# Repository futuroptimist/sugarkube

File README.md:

# 🍧 sugarkube

[![hardware boot][hardware-boot-badge]][pi-smoke-test-doc]

An accessible [k3s](https://k3s.io/) platform for Raspberry Pis and SBCs,
integrated with an off-grid solar setup.
The repository also covers the solar cube art installation, which powers aquarium air pumps and
small computers. It doubles as a living trellis—climbing plants weave through the aluminium
extrusions, while shade-loving herbs thrive beneath the panels. Hanging baskets can clip onto the
frame so the installation is surrounded by greenery.

### What's in a name?

"Sugarkube" refers to both the aluminium cube covered in solar panels **and**
the helper scripts that provide "syntactic sugar" for Kubernetes. Throughout
the docs you will see the term used in both contexts. The physical cube is
designed to be saturated with greenery: ground-level pots and grow bags tuck
between the uprights while hanging planters fill the airspace. Hardy
fruiting plants such as strawberries thrive in this arrangement and literally
embed glucose, fructose, and sucrose—the sugars that inspired the name—into the
structure's living canopy.

## Quick start: 3-node HA k3s cluster

New to sugarkube? Start with the 3-node HA happy path and follow it end-to-end:

- **[Happy path: 3-server HA cluster in two runs](docs/raspi_cluster_setup.md#happy-path-3-server-ha-cluster-in-two-runs)**
  — download the latest Pi image, flash, clone to SSD, bring up dev/staging/prod, and verify the
  cluster.
- **[Raspberry Pi cluster series](docs/index.md#raspberry-pi-cluster-series)** — Part 1/Part 2
  quick-starts plus manual walkthroughs when you want the raw commands.

## Application runbooks

- **[Generic app deployment contract](docs/app_deployment_contract.md)** — shared artifact,
  tag, chart, app-config, and `just app-*` command contract for all Sugarkube apps.
- **[Observability design](docs/observability-design.md)** — canonical Prometheus/Grafana
  design, ownership contract, privacy rules, dashboards, alerts, and release gates for Sugarkube,
  DSPACE, token.place, and danielsmith.io.
- **[Production power and network reliability](docs/production-power-network-reliability.md)**
  — draft cellular and battery design, measurement plan, and human validation gates.
- **[Node interface selection design](docs/node-interface-selection-design.md)**
  — K341 Ethernet/WiFi proposal, identity and quorum constraints, and qualification gates.
- **[Future-app onboarding guide](docs/app_onboarding.md)** — checklist and decision tree for
  adding apps such as wove and later services.
- **Current app runbooks** use the same GHCR-first staging, verification,
  promotion, rollback, and troubleshooting flow:
  - [DSPACE runbook](docs/apps/dspace.md) for `ghcr.io/democratizedspace/dspace`:
    [image workflow](https://github.com/democratizedspace/dspace/actions/workflows/ci-image.yml),
    [image package](https://github.com/democratizedspace/dspace/pkgs/container/dspace),
    [chart workflow](https://github.com/democratizedspace/dspace/actions/workflows/ci-helm.yml),
    [chart package listing](https://github.com/orgs/democratizedspace/packages?repo_name=dspace&q=charts%2Fdspace) (chart package page pending).
  - [token.place runbook](docs/apps/tokenplace.md) for `ghcr.io/futuroptimist/tokenplace-relay`:
    [image workflow](https://github.com/futuroptimist/token.place/actions/workflows/ci-image.yml),
    [image package](https://github.com/futuroptimist/token.place/pkgs/container/tokenplace-relay),
    [chart workflow](https://github.com/futuroptimist/token.place/actions/workflows/ci-helm.yml),
    [chart package](https://github.com/futuroptimist/token.place/pkgs/container/charts%2Ftokenplace).
  - [danielsmith.io runbook](docs/apps/danielsmith.md) for `ghcr.io/futuroptimist/danielsmith.io`:
    [image workflow](https://github.com/futuroptimist/danielsmith.io/actions/workflows/ci-image.yml),
    [image package](https://github.com/futuroptimist/danielsmith.io/pkgs/container/danielsmith.io),
    [chart workflow](https://github.com/futuroptimist/danielsmith.io/actions/workflows/ci-helm.yml),
    [chart package](https://github.com/futuroptimist/danielsmith.io/pkgs/container/charts%2Fdanielsmith).
  - [GitShelves runbook](docs/apps/gitshelves.md) for `ghcr.io/futuroptimist/gitshelves`:
    [image workflow](https://github.com/futuroptimist/gitshelves/actions/workflows/ci-image.yml),
    [image package](https://github.com/futuroptimist/gitshelves/pkgs/container/gitshelves),
    [chart workflow](https://github.com/futuroptimist/gitshelves/actions/workflows/ci-helm.yml),
    [chart package](https://github.com/futuroptimist/gitshelves/pkgs/container/charts%2Fgitshelves).
  - [jobbot3000 runbook](docs/apps/jobbot3000.md) for `ghcr.io/futuroptimist/jobbot3000`:
    [image workflow](https://github.com/futuroptimist/jobbot3000/actions/workflows/ci-image.yml),
    [image package](https://github.com/futuroptimist/jobbot3000/pkgs/container/jobbot3000),
    [chart workflow](https://github.com/futuroptimist/jobbot3000/actions/workflows/ci-helm.yml),
    [chart package](https://github.com/futuroptimist/jobbot3000/pkgs/container/charts%2Fjobbot3000).
- **Environment shortcuts:** token.place
  [dev](docs/k3s-tokenplace-dev.md), [staging](docs/k3s-tokenplace-staging.md), and
  [production](docs/k3s-tokenplace-prod.md); danielsmith.io
  [staging](docs/k3s-danielsmith-staging.md) and
  [production](docs/k3s-danielsmith-prod.md).

## Repository layout

- `cad/` — OpenSCAD models of structural parts. See
  [docs/pi_cluster_carrier.md](docs/pi_cluster_carrier.md) for the Pi carrier plate,
  [cad/solar_cube/panel_bracket.scad](cad/solar_cube/panel_bracket.scad) for the solar
  panel bracket with an `edge_radius` parameter (default 4 mm) to round its outer edges,
  and [cad/solar_cube/frame.scad](cad/solar_cube/frame.scad) for a parametric 2020 cube frame.
- `elex/` — KiCad and Fritzing electronics schematics including the `power_ring`
  board (see [elex/power_ring/specs.md](elex/power_ring/specs.md) and
  [docs/electronics_schematics.md](docs/electronics_schematics.md))
- `hardware/` — accessories like the Mac mini keyboard station cap (see
  [docs/mac_mini_station.md](docs/mac_mini_station.md))
- `docs/` — build instructions, safety notes, and learning resources
- [docs/start-here.md](docs/start-here.md) — quick orientation with 15-minute,
  day-one, and advanced reference tracks
- [docs/solar_basics.md](docs/solar_basics.md) — introduction to how solar panels generate
  power
- [docs/electronics_basics.md](docs/electronics_basics.md) — essential circuits and tools
- [docs/power_system_design.md](docs/power_system_design.md) — sizing batteries and
  charge controllers
- [docs/insert_basics.md](docs/insert_basics.md) — guide for heat-set inserts and printed threads
- [docs/network_setup.md](docs/network_setup.md) — connect the Pi cluster to your network
- [docs/lcd_mount.md](docs/lcd_mount.md) — optional 1602 LCD standoff locations
- [docs/pi_headless_provisioning.md](docs/pi_headless_provisioning.md) — headless boot playbook for
  `secrets.env` usage
- [docs/pi_carrier_launch_playbook.md](docs/pi_carrier_launch_playbook.md) — end-to-end launch
  playbook with a 10-minute fast path, persona walkthroughs, and deep reference maps
- [docs/pi_image_quickstart.md](docs/pi_image_quickstart.md) — build, flash, and boot the image
- [docs/pi_image_contributor_guide.md](docs/pi_image_contributor_guide.md) — map automation helpers
  to the docs that describe them
- [docs/pi_carrier_field_guide.md](docs/pi_carrier_field_guide.md) — printable checklist with a PDF
  companion (`docs/pi_carrier_field_guide.pdf`) for the workbench
- [user-data example](docs/templates/cloud-init/user-data.example) — SSH key and WiFi template
- `scripts/` — helper scripts for rendering and exports. See
  [docs/contributor_script_map.md](docs/contributor_script_map.md) for a
  contributor-facing map that ties each helper to the guide that explains it.
  - `download_pi_image.sh` — fetch the latest Pi image via the GitHub CLI; supports `--dry-run`
    metadata checks and reconciles `--dir`/`--output` directories with POSIX `test -ef`
    instead of `realpath` so macOS-friendly symlinks work without extra tooling.
    Invoke it from the unified CLI with
    `python -m sugarkube_toolkit pi download [--dry-run] [helper args...]` when you prefer
    a consistent entry point across automation helpers. The unified CLI always runs helpers
    from the repository root so relative paths to `scripts/` and docs work even when you
    launch it from nested directories. `tests/test_cli_docs_repo_root.py` guards the docs
    call-out by invoking `monkeypatch.chdir` to enter a temporary folder before
    running both `docs verify` and `docs simplify`. If you prefer, you can also run
    `python -m` commands from the repository root so the package can be imported cleanly;
    from a nested directory, `./scripts/sugarkube ...` (or adding `scripts/` to your `PATH`)
    bootstraps `PYTHONPATH` before forwarding to the CLI. Either way, the CLI executes
    helpers from the repository root so relative paths to scripts and docs remain stable.
  - `install_sugarkube_image.sh` — install the GitHub CLI when missing, download the
    latest release, verify checksums, expand the `.img.xz`, and emit a new
    `.img.sha256`; safe to run via `curl | bash`. Pass `--dry-run` to print the
    download/expansion plan without touching disk. Invoke it from the unified CLI with
    `python -m sugarkube_toolkit pi install [--dry-run] [helper args...]` when you want
    the same behavior without leaving the `sugarkube` entry point.
  - `collect_pi_image.sh` — normalize pi-gen output into a single `.img.xz`,
    clean up temporary work directories, use POSIX `test -ef` to compare paths
    without `realpath`, and fall back to `unzip` when `bsdtar` is unavailable
  - `build_pi_image.sh` — build a Raspberry Pi OS image with cloud-init and
    k3s preinstalled; embeds `pi_node_verifier.sh`, clones `token.place` and
    `democratizedspace/dspace` by default, and now ships node exporter,
    cAdvisor, Grafana Agent, and Netdata containers for observability. Customize
    branches with `TOKEN_PLACE_BRANCH` (default `main`) and `DSPACE_BRANCH`
    (default `v3`). Set `CLONE_SUGARKUBE=true` to include this repo and pass
    space-separated Git URLs via `EXTRA_REPOS` to clone additional projects;
    needs a valid `user-data.yaml` and ~10 GB free disk space. Set `DEBUG=1` to
    trace script execution.
  - `flash_pi_media.sh` — stream `.img` or `.img.xz` directly to removable
    media with SHA-256 verification and automatic eject. A PowerShell wrapper
    (`flash_pi_media.ps1`) shells out to the same Python core on Windows.
  - `pi_node_verifier.sh` — check k3s prerequisites; use `--json` for machine output,
    `--full` to print text plus the JSON summary in one run, or `--help` for usage
  - `pi_smoke_test.py` — SSH wrapper that runs the verifier remotely, supports reboot checks,
    and emits JSON summaries for CI harnesses
  - `collect_support_bundle.py` — gather Kubernetes, systemd, and Docker diagnostics into timestamped
    archives. Invoke it from the unified CLI with
    `python -m sugarkube_toolkit pi support-bundle [--dry-run] [args...]` when you want the same
    workflow without leaving the `sugarkube` entry point. The CLI `--dry-run` flag prints the
    helper invocation without executing it so you can confirm the host and arguments before running
    the collection (guarded by
    `tests/test_sugarkube_toolkit_cli.py::test_pi_support_bundle_invokes_helper`).
  - `sugarkube_doctor.sh` — chain download dry-runs, flash validation, and linting checks. Invoke it
    from the unified CLI with `python -m sugarkube_toolkit doctor [--dry-run] [-- args...]` to avoid
    memorizing the standalone helper.
  - `render_field_guide_pdf.py` — build the Markdown field guide into a single-page PDF without
    extra pip dependencies so releases can refresh the printable checklist automatically
  - `scan-secrets.py` — scan diffs for high-risk patterns using `ripsecrets` when
    available and also run a regex check to catch common tokens
- `outages/` — structured outage records (see
  [docs/outage_catalog.md](docs/outage_catalog.md))
- `tests/` — quick checks for helper scripts and documentation

## Pi image releases

Use the `pi-image` workflow when you need a fresh on-demand workflow artifact
for reimaging Raspberry Pi nodes; open **Actions → pi-image → Run workflow** (or let the
cluster bootstrap helper dispatch it) and download the `sugarkube-img` artifact.
Use `pi-image-release` only when a maintainer intentionally needs to publish the
latest signed GitHub Release. That manual release-publisher workflow builds the
image, optionally boots it in QEMU, signs release assets with cosign when
publishing is enabled, and attaches `sugarkube.img.xz`, its checksum, a
provenance manifest, and the full `pi-gen` build log to the release. Release
notes summarize stage timings and link directly to the manifest so you can
verify the build inputs and commit hashes before flashing. Run
`./scripts/install_sugarkube_image.sh` (or fetch the same helper
 via `curl -fsSL https://raw.githubusercontent.com/futuroptimist/sugarkube/main/scripts/install_sugarkube_image.sh | bash`) to
 download, verify, and expand the latest release. When you prefer a task runner,
use either `sudo make flash-pi FLASH_DEVICE=/dev/sdX` or `sudo FLASH_DEVICE=/dev/sdX just flash-pi` to
chain download → verification → flashing with the streaming helper. Prefer go-task? Run
`sudo task pi:flash FLASH_DEVICE=/dev/sdX` to reach the same helper via the Taskfile. Need to forward
additional helper flags? Append `PI_FLASH_ARGS="-- --force"` (or similar) alongside `FLASH_DEVICE`
so both the device and extra arguments are preserved. The recipe variables read `FLASH_DEVICE`
(and optional `DOWNLOAD_ARGS`) from the environment, so prefix the variable as shown. Regression coverage:
`tests/test_taskfile.py::test_taskfile_pi_flash_forwards_flash_device` keeps the go-task wrapper aligned with
these instructions. Both the Makefile, justfile, and Taskfile expose
`download-pi-image`, `install-pi-image`,
`doctor`, and `codespaces-bootstrap`
shortcuts so GitHub
Codespaces users can install prerequisites and flash media without additional shell glue—pick the runner
you prefer (`make codespaces-bootstrap`, `just codespaces-bootstrap`, or `task codespaces-bootstrap`). Go-task
users can also call the hyphenated aliases directly (`task download-pi-image`, `task install-pi-image`),
which forward `DOWNLOAD_ARGS` the same way as the Make and just wrappers. Regression coverage:
`tests/test_codespaces_bootstrap.py` keeps the package lists aligned across each wrapper, and
`tests/test_taskfile.py::test_taskfile_includes_make_style_aliases` ensures the Taskfile mirrors the
documented shortcuts.
`./scripts/sugarkube-latest` remains available when you only need the `.img.xz` artifact with
checksum verification.
Prefer a unified entry point? Run `python -m sugarkube_toolkit pi download --dry-run` from the
repository root to preview the release helper. Once running, the CLI forces the working directory to
the repository root before invoking helpers. Working from a nested directory? Call
`./scripts/sugarkube pi download --dry-run` (or add `scripts/` to your `PATH`) so the wrapper
bootstraps `PYTHONPATH` before forwarding to the CLI. When prerequisites such as the GitHub CLI,
`curl`, or `sha256sum` are missing, the dry-run prints reminders instead of aborting so you can
review the planned commands first. Need the combined installer that downloads and
expands the image? Run

```bash
python -m sugarkube_toolkit pi install --dry-run -- --dir ~/sugarkube/images --image ~/sugarkube/images/sugarkube.img
```

Drop `--dry-run` once you are ready; flags after the standalone `--` flow directly to
`scripts/install_sugarkube_image.sh`.

Reuse the streaming helper via:

```bash
python -m sugarkube_toolkit pi flash --dry-run -- --image ~/sugarkube/images/sugarkube.img --device /dev/sdX
```

Drop `--dry-run` when you're ready to write media.

Prefer a guided experience? Open [docs/flash-helper/](docs/flash-helper/) to paste a workflow run
URL and receive OS-specific download, verification, and flashing steps. The same logic is also
available via `python scripts/workflow_flash_instructions.py --help` for command-line use.

Run `pre-commit run --all-files` before committing.
This triggers `scripts/checks.sh`, which installs required tooling and runs
linters, tests, and documentation checks. If you send patches with `git send-email`,
copy [`hooks/sendemail-validate.sample`](hooks/sendemail-validate.sample) to
`.git/hooks/sendemail-validate` so the email workflow executes the same checks
after applying your series and scans each patch for secrets before sending.
The helper now bootstraps the [`just`](https://github.com/casey/just) binary automatically when it
is missing so the formatting and orchestration recipes never skip; run
`./scripts/install_just.sh` directly when you want to install the tool ahead of the
full check suite.
Running the checks as a non-root user now exports `ALLOW_NON_ROOT=1` and sets
`BATS_CWD`/`BATS_LIB_PATH` to the repository root so Bats fixtures resolve the
same way they do in CI. Overriding `ALLOW_NON_ROOT` with any value other than
`1` causes an immediate failure instead of a confusing permission error.
Regression coverage:
`tests/test_sendemail_validate_hook.py::test_sendemail_hook_runs_repo_checks`
and
`tests/test_sendemail_validate_hook.py::test_sendemail_hook_scans_patches_for_secrets`,
plus `tests/checks_script_test.py::test_exports_test_env_defaults` and
`tests/checks_script_test.py::test_rejects_conflicting_allow_non_root`.

### Integration tests

Set `AVAHI_AVAILABLE=1` to opt into the Avahi-backed mDNS roundtrip test. The
integration suite expects `avahi-publish`, `avahi-browse`, and `avahi-resolve`
to be installed. Run it directly with:

```bash
AVAHI_AVAILABLE=1 bats tests/integration/mdns_roundtrip.bats
```

When you run the broader pytest suite in minimal containers, set
`SUGARKUBE_ALLOW_TOOL_SHIMS=1` to let `tests.conftest.require_tools` create
temporary stand-ins for missing binaries (for example, `ip` and `ping`). Provide
`SUGARKUBE_TOOL_SHIM_DIR=/tmp/shims` to control where the executables are
written. Shims are happy-path stubs that always return exit code ``0`` and the
shim directory is prepended to ``PATH`` while enabled, so prefer using them in
isolated test environments (such as disposable containers or dedicated
virtualenvs) instead of your daily shell. Regression coverage:
`tests/test_require_tools.py::test_require_tools_falls_back_to_shims`.
When installers are unavailable, `require_tools` now reuses the same shim
fallback controlled by `SUGARKUBE_PREINSTALL_TOOL_SHIMS` (defaults to `"1"`) so
per-test checks avoid skipping in constrained environments. Regression coverage:
`tests/test_require_tools.py::test_require_tools_shims_after_install_failure_with_preinstall_enabled`.
When `apt-get` is unavailable, the session-level pre-install hook now shims the
core CLI dependencies ahead of time so integration tests see the expected tools
without waiting for per-test skip handling. Set
`SUGARKUBE_PREINSTALL_TOOL_SHIMS=0` to opt out when you need to exercise real
installations instead of stubs. Regression coverage:
`tests/test_require_tools.py::test_preinstall_test_cli_tools_shims_when_installs_blocked`
and `tests/test_require_tools.py::test_preinstall_test_cli_tools_shim_opt_out`.
Network namespace probes now request the `ip` and `unshare` utilities up front,
falling back to the same tooling installer before retrying with sudo so CI and
local runs converge. Regression coverage:
`tests/test_ensure_root_privileges.py::test_ensure_root_privileges_installs_netns_tools_first`.
Set `SUGARKUBE_NETNS_FALLBACK=xfail` when you want missing network namespace
privileges to be recorded as expected failures instead of skips so the suite
highlights the capability gap without hiding it. Regression coverage:
`tests/test_ensure_root_privileges.py::test_ensure_root_privileges_xfails_when_requested`.

For mDNS end-to-end coverage that depends on network namespaces, set
`SUGARKUBE_ALLOW_NETNS_STUBS=1` when your environment lacks `CAP_NET_ADMIN` or
non-interactive `sudo`. Use `SUGARKUBE_ALLOW_NETNS_STUBS=auto` to attempt real
namespace setup but fall back to stubs on permission errors. The stub yields
deterministic namespace metadata and lets the suite skip only the
multicast-dependent assertions instead of failing when namespace setup is
unavailable. Regression coverage:
`tests/test_netns_stub.py::test_netns_stub_flag_enables_stubbed_environment` and
`tests/test_netns_stub.py::test_netns_stub_auto_mode_falls_back_on_permission_errors`.

[hardware-boot-badge]: https://img.shields.io/endpoint?url=https://raw.githubusercontent.com/futuroptimist/sugarkube/main/docs/status/hardware-boot.json
[pi-smoke-test-doc]: docs/pi_smoke_test.md

## Getting Started

```bash
git clone https://github.com/futuroptimist/sugarkube.git
# or with SSH:
# git clone git@github.com:futuroptimist/sugarkube.git
cd sugarkube
pip install pre-commit pyspelling linkchecker
pre-commit install
pre-commit run --all-files
```

If you update documentation, install `aspell` and verify spelling and links.
Prefer the combined helper when editing Markdown so spellcheck and link checks stay aligned with the
automation mapping surfaced in [docs/pi_image_contributor_guide.md](docs/pi_image_contributor_guide.md):

```bash
make docs-verify
# or
just docs-verify
# or
task docs:verify
```

Both commands shell into the unified CLI via `scripts/sugarkube docs verify`, which in turn runs
`python -m sugarkube_toolkit docs verify`. The CLI executes the same `pyspelling -c .spellcheck.yaml`
and `linkchecker --no-warnings README.md docs/` commands documented throughout the repo. Provide
`DOCS_VERIFY_ARGS="--dry-run"` to preview the commands before they execute. `pyspelling` relies on
`aspell` and the English dictionary (`aspell-en`); install them manually when the helper cannot. The
`scripts/checks.sh` helper attempts to install the dependencies via `apt-get` when missing. When you
want Sugarkube to bootstrap the prerequisites automatically without running the full lint suite, use
the docs
simplification target instead:

```bash
make docs-simplify
# or
just simplify-docs
# or
task docs:simplify
```

Both wrappers call the unified CLI (`sugarkube docs simplify`), which shells into
`scripts/checks.sh --docs-only` to install `pyspelling`, `linkchecker`, and `aspell` before running
the documentation checks. Add `--skip-install` when those dependencies already exist so the helper
reuses the current environment instead of invoking `apt-get` or `pip`. The helper falls back to
`python -m pip` automatically when a standalone `pip` shim is missing so minimal environments still
bootstrap correctly. When you need to run the commands directly:

```bash
sudo apt-get install aspell aspell-en  # Debian/Ubuntu
brew install aspell                    # macOS
pyspelling -c .spellcheck.yaml
linkchecker --no-warnings README.md docs/
```

Prefer the unified CLI? `python -m sugarkube_toolkit docs simplify [--dry-run] [-- args...]`
wraps the same `scripts/checks.sh --docs-only` helper so you can stay inside a single entry point.
Additional arguments after `--` are forwarded directly to the script.
Regression coverage: `tests/checks_script_test.py::test_runs_js_checks_when_package_lock_present`
verifies the helper runs `npm run test:ci` alongside linting and formatting when Node tooling exists,
`tests/checks_script_test.py::test_docs_only_skip_install_uses_existing_tools` exercises the docs-only
`--skip-install` path, and `tests/checks_script_test.py::test_skip_install_avoids_dependency_bootstrap`
covers full runs that reuse preinstalled tooling. `tests/test_docs_verify_wrapper.py::
test_make_docs_verify_runs_cli` exercises the Make target in dry-run mode so these instructions stay
accurate.

The `--no-warnings` flag prevents linkchecker from returning a non-zero exit code on benign Markdown
parsing warnings.

Scan staged changes for secrets before committing:

```bash
git diff --cached | ./scripts/scan-secrets.py
```

If the repository includes a `package.json` but `npm` or `package-lock.json`
are missing, `scripts/checks.sh` will warn and skip JavaScript-specific
checks.

STL files are produced automatically by CI for each OpenSCAD model and can be
downloaded from the workflow run. Provide a single `.scad` file path to render a
variant locally. The script accepts only one argument and prints a usage
message if others are supplied:

```bash
bash scripts/openscad_render.sh cad/pi_cluster/pi5_triple_carrier_rot45.scad
STANDOFF_MODE=printed bash scripts/openscad_render.sh cad/pi_cluster/pi5_triple_carrier_rot45.scad
STANDOFF_MODE=nut bash scripts/openscad_render.sh cad/pi_cluster/pi5_triple_carrier_rot45.scad
```

By default the script uses the model's `standoff_mode` value (`heatset`).
Set `STANDOFF_MODE=printed` to generate 3D-printed threads or `STANDOFF_MODE=nut` for a
captive hex recess. Values are case-insensitive and ignore surrounding whitespace;
`heatset`, `printed`, and `nut` are accepted. Supplying only whitespace uses the model's
default `standoff_mode`.

The helper script validates that the provided `.scad` file exists and that
OpenSCAD is available in `PATH`, printing a helpful error if either check fails.
It separates options from the file path with `--` and handles filenames
that begin with a dash, whether absolute or relative.
The `.scad` extension is matched case-insensitively without Bash 4 features, so
`MODEL.SCAD` works even on macOS default Bash 3.2.

## Community

See [CONTRIBUTING.md](CONTRIBUTING.md) for ways to help.
Participation is governed by the [Code of Conduct](CODE_OF_CONDUCT.md).

See [AGENTS.md](AGENTS.md) for included LLM assistants.
See [llms.txt](llms.txt) for an overview suitable for language models.

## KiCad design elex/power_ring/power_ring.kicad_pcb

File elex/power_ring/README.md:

# Power Ring KiCad Project

The **power_ring** directory contains a minimal KiCad design used as a starting point for the Sugarkube power distribution board.  The project is based on KiCad's `custom_pads_test` demo and demonstrates basic footprint libraries and schematic symbols.  It currently exports a small two–layer board that can be iterated on for real hardware.  High‑level requirements live in [specs.md](specs.md).

Included files:

- `power_ring.kicad_pro` – project settings
- `power_ring.kicad_sch` – schematic
- `power_ring.kicad_pcb` – PCB layout
- `power_ring.kicad_sym` and `power_ring_schlib.kicad_sym` – symbol libraries
- `power_ring.pretty/` – footprint library

A title block comment reminds you to place decoupling capacitors near power pins,
a second note encourages keeping high-current traces short for better performance,
a third note urges labeling polarity and voltage on connectors to avoid wiring mistakes,
and a fourth note reminds you to verify KiBot exports before fabrication.

Open the project in **KiCad 9** or newer and modify the schematic to suit your power distribution needs (for example, add screw terminals, fuses and test points).  Use [KiBot](https://github.com/INTI-CMNB/KiBot) with `.kibot/power_ring.yaml` or run the GitHub workflow to produce Gerber files, a PDF schematic and a BOM in `build/power_ring/`.

The layout now includes a "SugarKube" copper label for easy identification.

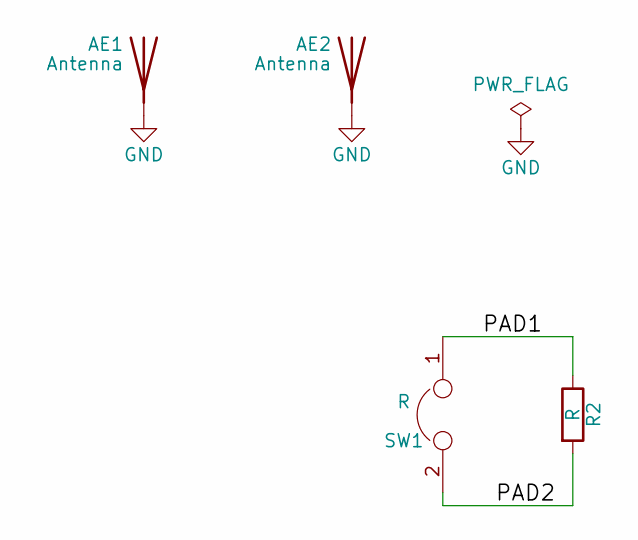
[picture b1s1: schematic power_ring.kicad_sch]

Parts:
AE1, AE2: Antenna
R2: R
SW1: R

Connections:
/PAD1: R2.1, SW1.1
/PAD2: R2.2, SW1.2
GND: AE1.1 (A), AE2.1 (A)

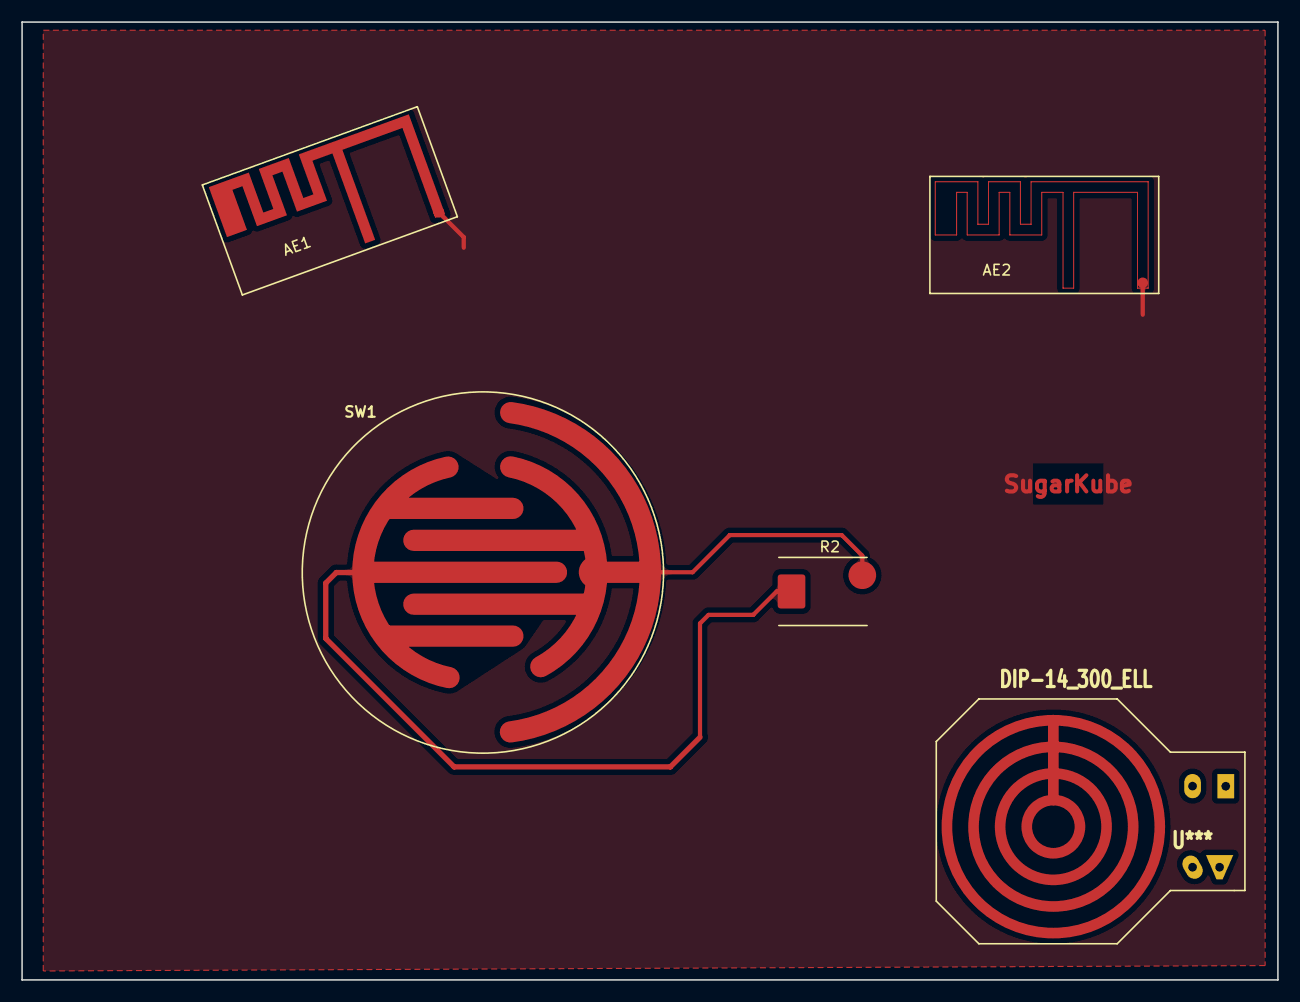
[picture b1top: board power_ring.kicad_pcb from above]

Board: 2 copper layers, 118.0 x 90.0 mm, 5 parts (0 on the bottom side), 3 nets.

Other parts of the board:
U***: DIP-14_300_ELL; DIP-14__300_ELL
